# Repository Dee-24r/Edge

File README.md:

## This is EDGE, my Split Keyboard! 30 keys (can you beat that?) and three layers to cover almost all keyboard inputs! There's the normal, number, and bluetooth layers!

Please note that the firmware files are in a different repo: 
https://github.com/Dee-24r/zmk-config-edge

<br>
**Physical pcb arrived 3 days ago, I'l assemble soon!**

Here are pictures of my design files

# build!

[https://github.com/Dee-24r/Edge/blob/main/images/malfunctioning_keeb.mp4](https://github.com/user-attachments/assets/b93cf569-b797-47ab-8092-d4cc0c10ea89)

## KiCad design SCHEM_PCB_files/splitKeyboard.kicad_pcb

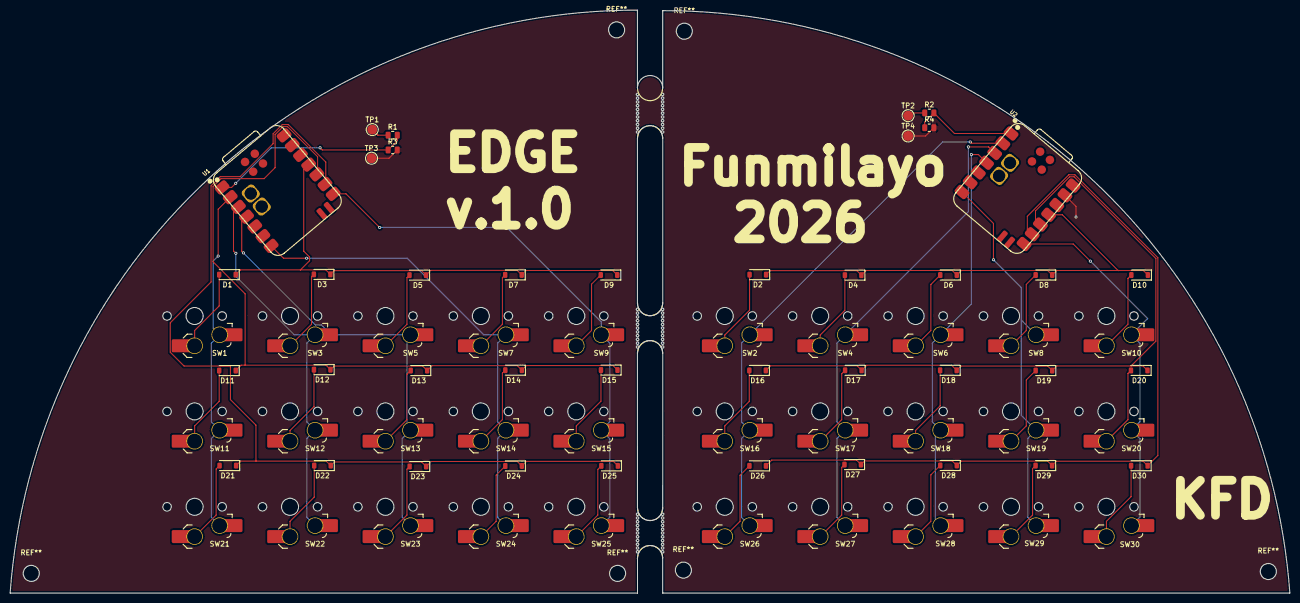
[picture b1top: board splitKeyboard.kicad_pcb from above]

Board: 2 copper layers, 255.5 x 116.4 mm, 73 parts (0 on the bottom side), 41 nets.

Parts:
D1, D2, D3, D4, D5, D6, D7, D8, D9, D10, D11, D12, D13, D14, D15, D16, D17, D18, D19, D20, D21, D22, D23, D24, D25, D26, D27, D28, D29, D30: D; D_SOD-123
H1, H2, H4: MountingHole; mouse-bite-5mm-slot
R1, R2: 806k; R_0805_2012Metric
R3, R4: 2M; R_0805_2012Metric
SW1, SW2, SW3, SW4, SW5, SW6, SW7, SW8, SW9, SW10, SW11, SW12, SW13, SW14, SW15, SW16, SW17, SW18, SW19, SW20, SW21, SW22, SW23, SW24, SW25, SW26, SW27, SW28, SW29, SW30: SW_Push; SW_choc_v1_HS_CPG135001S30_1u
TP1, TP2: BAT; TestPoint_Pad_D2.0mm
TP3, TP4: GND; TestPoint_Pad_D2.0mm
U1, U2: XIAO-nRF52840-SMD; modified-XIAO-nRF52840-SMD

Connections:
BT_PIN: R1.2, R2.2, R3.1, R4.1, U1.1 (P0.02_A0_D0), U2.1 (P0.02_A0_D0)
COL 0: SW1.1, SW2.1, SW11.1, SW16.1, SW21.1, SW26.1, U1.2 (P0.03_A1_D1), U2.2 (P0.03_A1_D1)
COL 1: SW3.1, SW4.1, SW12.1, SW17.1, SW22.1, SW27.1, U1.3 (P0.28_A2_D2), U2.3 (P0.28_A2_D2)
COL 2: SW5.1, SW6.1, SW13.1, SW18.1, SW23.1, SW28.1, U1.4 (P0.29_A3_D3), U2.4 (P0.29_A3_D3)
COL 3: SW7.1, SW8.1, SW14.1, SW19.1, SW24.1, SW29.1, U1.7 (P1.11_D6_TX), U2.7 (P1.11_D6_TX)
COL 4: SW9.1, SW10.1, SW15.1, SW20.1, SW25.1, SW30.1, U1.8 (P1.12_D7_RX), U2.8 (P1.12_D7_RX)
GND: R3.2, R4.2, TP3.1 (1_1), TP4.1 (1_1), U1.13 (GND), U2.13 (GND)
unnamed: D1.2 (A), SW1.2
unnamed: D2.2 (A), SW2.2
unnamed: D3.2 (A), SW3.2
unnamed: D4.2 (A), SW4.2
unnamed: D5.2 (A), SW5.2
unnamed: D6.2 (A), SW6.2
unnamed: D7.2 (A), SW7.2
unnamed: D8.2 (A), SW8.2
unnamed: D9.2 (A), SW9.2
unnamed: D10.2 (A), SW10.2
unnamed: D11.2 (A), SW11.2
unnamed: D12.2 (A), SW12.2
unnamed: D13.2 (A), SW13.2
unnamed: D14.2 (A), SW14.2
unnamed: D15.2 (A), SW15.2
unnamed: D16.2 (A), SW16.2
unnamed: D17.2 (A), SW17.2
unnamed: D18.2 (A), SW18.2
unnamed: D19.2 (A), SW19.2
unnamed: D20.2 (A), SW20.2
unnamed: D21.2 (A), SW21.2
unnamed: D22.2 (A), SW22.2
unnamed: D23.2 (A), SW23.2
unnamed: D24.2 (A), SW24.2
unnamed: D25.2 (A), SW25.2
unnamed: D26.2 (A), SW26.2
unnamed: D27.2 (A), SW27.2
unnamed: D28.2 (A), SW28.2
unnamed: D29.2 (A), SW29.2
unnamed: D30.2 (A), SW30.2
ROW 0: D1.1 (K), D2.1 (K), D3.1 (K), D4.1 (K), D5.1 (K), D6.1 (K), D7.1 (K), D8.1 (K), D9.1 (K), D10.1 (K), U1.11 (P1.15_D10_MOSI), U2.11 (P1.15_D10_MOSI)
ROW 1: D11.1 (K), D12.1 (K), D13.1 (K), D14.1 (K), D15.1 (K), D16.1 (K), D17.1 (K), D18.1 (K), D19.1 (K), D20.1 (K), U1.10 (P1.14_D9_MISO), U2.10 (P1.14_D9_MISO)
ROW 2: D21.1 (K), D22.1 (K), D23.1 (K), D24.1 (K), D25.1 (K), D26.1 (K), D27.1 (K), D28.1 (K), D29.1 (K), D30.1 (K), U1.9 (P1.13_D8_SCK), U2.9 (P1.13_D8_SCK)
VBAT: R1.1, R2.1, TP1.1 (1_1), TP2.1 (1_1)

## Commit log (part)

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2026-05-04 BOM, Initial commit
2026-05-04 Added main files
2026-05-04 added mounting holes to my pcb
2026-05-04 updated pics
